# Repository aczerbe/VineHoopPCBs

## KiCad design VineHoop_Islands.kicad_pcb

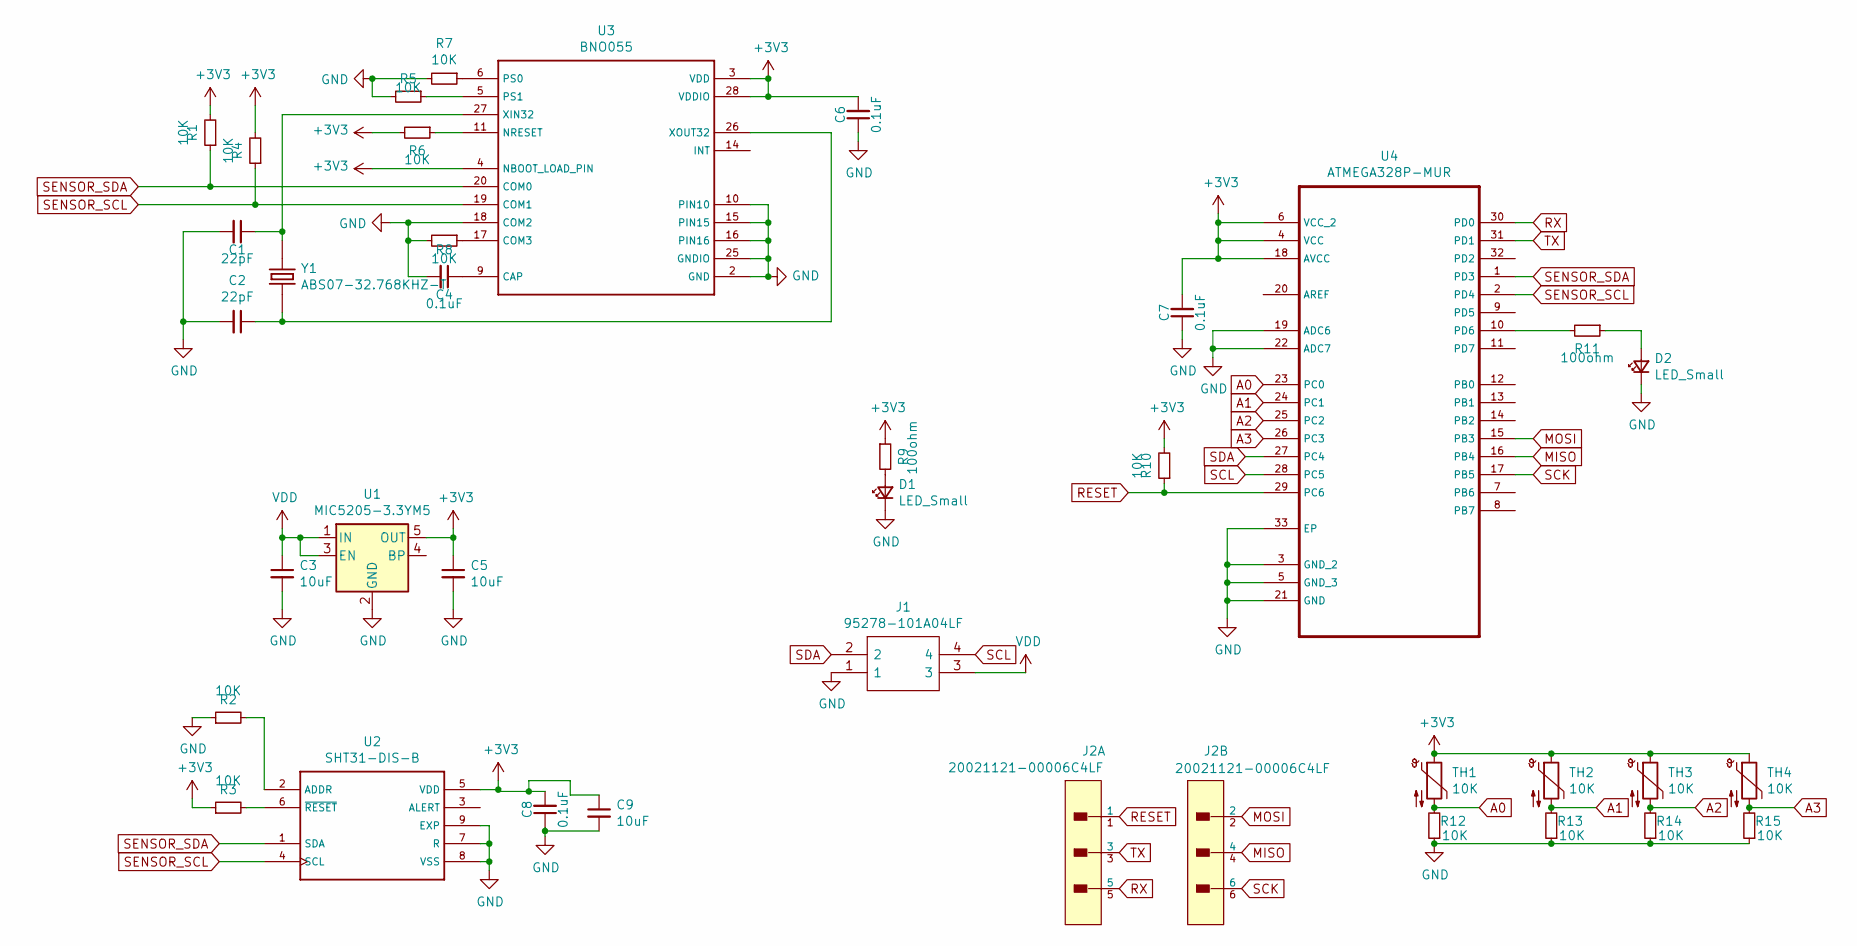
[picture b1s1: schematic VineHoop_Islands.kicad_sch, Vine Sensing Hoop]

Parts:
C1, C2: 22pF; C_0603_1608Metric
C3, C5, C9: 10uF; C_0603_1608Metric
C4, C6, C7, C8: 0.1uF; C_0603_1608Metric
D1, D2: LED_Small; LED_0603_1608Metric
J1: 95278-101A04LF; 95278101A04LF; Manufacturer_Part_Number 95278-101A04LF; Mouser Part Number 649-95278-101A04LF
J2: 20021121-00006C4LF; Amphenol_ICC___FCI-20021121-00006C4LF-MFG; current rating 1A; voltage rating 125V; mouser part number 649-202112100006C4LF; digikey description CONN HEADER SMD 6POS 1.27MM
R1, R2, R3, R4, R5, R6, R7, R8, R10, R12, R13, R14, R15: 10K; R_0603_1608Metric
R9, R11: 100ohm; R_0603_1608Metric
TH1, TH2, TH3, TH4: 10K; R_0603_1608Metric
U1: MIC5205-3.3YM5; SOT-23-5
U2: SHT31-DIS-B; XDCR_SHT31-DIS-F2.5KS
U3: BNO055; LGA28R50P4X10_380X520X100
U4: ATMEGA328P-MUR; QFN50P500X500X100-33N
Y1: ABS07-32.768KHZ-T; XTAL_ABS07-32.768KHZ-T

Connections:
+3V3: C5.1, C6.2, C7.2, C8.2, C9.1, R1.2, R3.1, R4.2, R6.2, R9.1, R10.2, TH1.1, TH2.1, TH3.1, TH4.1, U1.5 (OUT), U2.5 (VDD), U3.3 (VDD), U3.4 (NBOOT_LOAD_PIN), U3.28 (VDDIO), U4.4 (VCC), U4.6 (VCC_2), U4.18 (AVCC)
A0: R12.2, TH1.2, U4.23 (PC0)
A1: R13.2, TH2.2, U4.24 (PC1)
A2: R14.2, TH3.2, U4.25 (PC2)
A3: R15.2, TH4.2, U4.26 (PC3)
GND: C1.2, C2.2, C3.2, C4.2, C5.2, C6.1, C7.1, C8.1, C9.2, D1.1 (K), D2.1 (K), J1.1, R2.1, R5.2, R7.2, R8.2, R12.1, R13.1, R14.1, R15.1, U1.2 (GND), U2.7 (R), U2.8 (VSS), U2.9 (EXP), U3.2 (GND), U3.10 (PIN10), U3.15 (PIN15), U3.16 (PIN16), U3.18 (COM2), U3.25 (GNDIO), U4.3 (GND_2), U4.5 (GND_3), U4.19 (ADC6), U4.21 (GND), U4.22 (ADC7), U4.33 (EP)
MISO: J2.4, U4.16 (PB4)
MOSI: J2.2, U4.15 (PB3)
unnamed: C1.1, U3.27 (XIN32), Y1.1
unnamed: C2.1, U3.26 (XOUT32), Y1.2
unnamed: C4.1, U3.9 (CAP)
unnamed: D1.2 (A), R9.2
unnamed: D2.2 (A), R11.1
unnamed: R2.2, U2.2 (ADDR)
unnamed: R3.2, U2.6 (~RESET~)
unnamed: R5.1, U3.5 (PS1)
unnamed: R6.1, U3.11 (NRESET)
unnamed: R7.1, U3.6 (PS0)
unnamed: R8.1, U3.17 (COM3)
unnamed: R11.2, U4.10 (PD6)
RESET: J2.1, R10.1, U4.29 (PC6)
RX: J2.5, U4.30 (PD0)
SCK: J2.6, U4.17 (PB5)
SCL: J1.4, U4.28 (PC5)
SDA: J1.2, U4.27 (PC4)
SENSOR_SCL: R4.1, U2.4 (SCL), U3.19 (COM1), U4.2 (PD4)
SENSOR_SDA: R1.1, U2.1 (SDA), U3.20 (COM0), U4.1 (PD3)
TX: J2.3, U4.31 (PD1)
VDD: C3.1, J1.3, U1.1 (IN), U1.3 (EN)

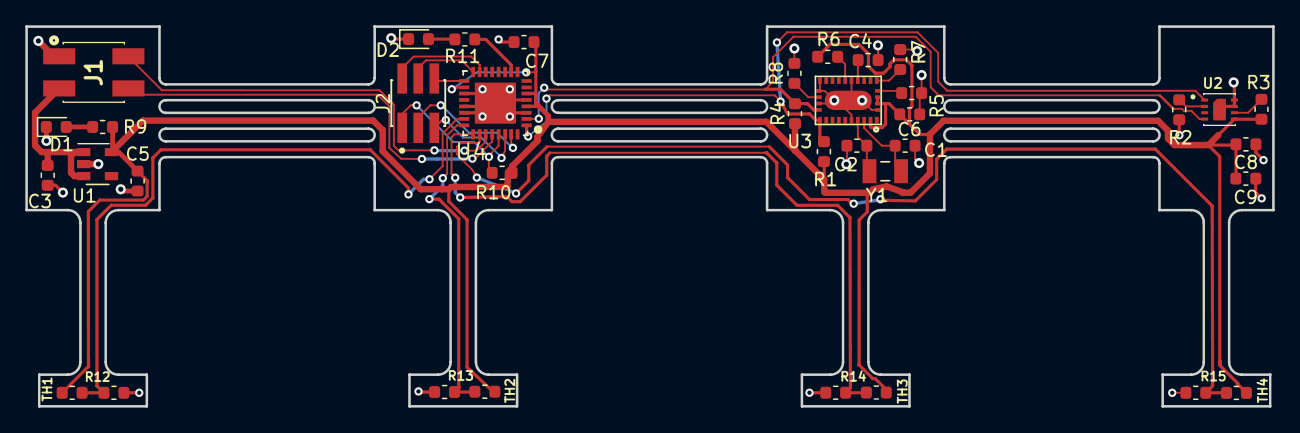
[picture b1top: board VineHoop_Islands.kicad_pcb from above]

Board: 2 copper layers, 98.5 x 30.0 mm, 37 parts (0 on the bottom side), 29 nets.

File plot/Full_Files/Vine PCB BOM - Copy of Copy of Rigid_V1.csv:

Item,Designator,Qty,Manufacturer,Manufacturer P/N,Description
1,"C1, C2, C7, C8",4,Yageo,CC0603JRNPO9BN220,22pF ceramic cap (any is fine)
2,"C3, C5",2,AVX Corporation,F981A106MMA,10uF tantalum cap (any is fine)
3,"C4, C6, C9",3,KEMET,C0603C104Z3VACTU,0.1uF ceramic (any is fine)
4,"D1, D2",2,Broadcom Limited,HSMC-C190,LED indicators
5,"J1, J2",2,Sullins Connector Solutions,NPTC061KFXC-RC,"1x06 0.1"" pitch SMD header"
6,J3,1,Sullins Connector Solutions,NPTC041KFXC-RC,"1x04 0.1"" pitch SMD header"
7,"R1, R2, R3, R4, R5, R6, R7, R8, R9",9,Yageo,RC0603FR-0710KL,10K
8,"R10, R11",2,Yageo,RC0603FR-07100RL,100ohm
9,U1,1,Microchip Technology,MIC5205-3.3YM5-TR,MIC5205-3.3YM5 3.3v regulator
10,U2,1,Sensirion AG,SHT31-DIS-B2.5KS,SHT31-DIS-B Temp/Humidity Sensor
11,U3,1,Bosch Sensortec,BNO055,Bosch BNO055 IMU
12,U4,1,Microchip Technology,ATMEGA328P-MU,ATMEGA328P-MU Microcontroller
13,Y1,1,EPSON,FC-135 32.7680KA-A5,32.768kHz
14,Y2,1,TXC CORPORATION,7A-16.000MAAE-T,16MHz Crystal

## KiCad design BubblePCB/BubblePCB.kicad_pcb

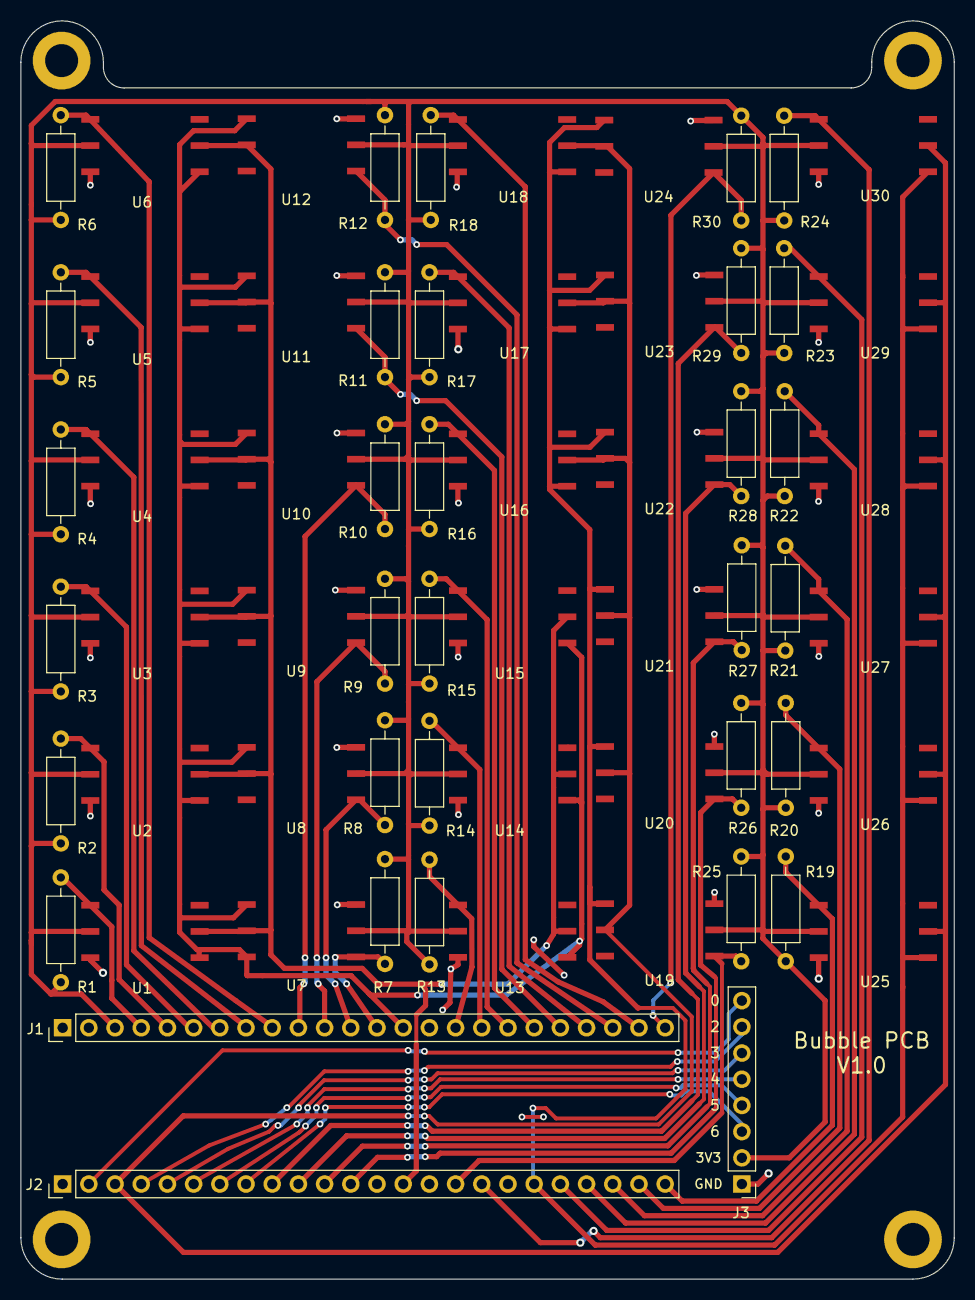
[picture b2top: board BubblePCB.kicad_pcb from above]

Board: 2 copper layers, 90.5 x 122.0 mm, 64 parts (0 on the bottom side), 44 nets.

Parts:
J1, J2: Conn_01x24_Female; PinHeader_1x24_P2.54mm_Vertical
J3: Conn_01x07_Male; PinHeader_1x08_P2.54mm_Vertical
R1, R2, R3, R4, R5, R6, R7, R8, R9, R10, R11, R12, R13, R14, R15, R16, R17, R18, R19, R20, R21, R22, R23, R24, R25, R26, R27, R28, R29, R30: 3.3k; R_Axial_DIN0207_L6.3mm_D2.5mm_P10.16mm_Horizontal
U1, U2, U3, U4, U5, U6, U7, U8, U9, U10, U11, U12, U13, U14, U15, U16, U17, U18, U19, U20, U21, U22, U23, U24, U25, U26, U27, U28, U29, U30: ABPMANN060KGSA3
a: MountingHole_3.2mm_M3_DIN965_Pad

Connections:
+3V3: J1.3, J2.15, J3.2, R1.2, R2.2, R3.2, R4.2, R5.2, R6.2, R7.2, R8.2, R9.2, R10.2, R11.2, R12.2, R13.2, R14.2, R15.2, R16.2, R17.2, R18.2, R19.2, R20.2, R21.2, R22.2, R23.2, R24.2, R25.2, R26.2, R27.2, R28.2, R29.2, R30.2, U1.2 (Vcc), U2.2 (Vcc), U3.2 (Vcc), U4.2 (Vcc), U5.2 (Vcc), U6.2 (Vcc), U7.2 (Vcc), U8.2 (Vcc), U9.2 (Vcc), U10.2 (Vcc), U11.2 (Vcc), U12.2 (Vcc), U13.2 (Vcc), U14.2 (Vcc), U15.2 (Vcc), U16.2 (Vcc), U17.2 (Vcc), U18.2 (Vcc), U19.2 (Vcc), U20.2 (Vcc), U21.2 (Vcc), U22.2 (Vcc), U23.2 (Vcc), U24.2 (Vcc), U25.2 (Vcc), U26.2 (Vcc), U27.2 (Vcc), U28.2 (Vcc), U29.2 (Vcc), U30.2 (Vcc)
GND: J1.2, J1.15, J2.1, J3.1, U1.1 (GND), U2.1 (GND), U3.1 (GND), U4.1 (GND), U5.1 (GND), U6.1 (GND), U7.1 (GND), U8.1 (GND), U9.1 (GND), U10.1 (GND), U11.1 (GND), U12.1 (GND), U13.1 (GND), U14.1 (GND), U15.1 (GND), U16.1 (GND), U17.1 (GND), U18.1 (GND), U19.1 (GND), U20.1 (GND), U21.1 (GND), U22.1 (GND), U23.1 (GND), U24.1 (GND), U25.1 (GND), U26.1 (GND), U27.1 (GND), U28.1 (GND), U29.1 (GND), U30.1 (GND)
MISO: J2.14, U1.5 (MISO), U2.5 (MISO), U3.5 (MISO), U4.5 (MISO), U5.5 (MISO), U6.5 (MISO), U7.5 (MISO), U8.5 (MISO), U9.5 (MISO), U10.5 (MISO), U11.5 (MISO), U12.5 (MISO), U13.5 (MISO), U14.5 (MISO), U15.5 (MISO)
MISO1: J2.3, U16.5 (MISO), U17.5 (MISO), U18.5 (MISO), U19.5 (MISO), U20.5 (MISO), U21.5 (MISO), U22.5 (MISO), U23.5 (MISO), U24.5 (MISO), U25.5 (MISO), U26.5 (MISO), U27.5 (MISO), U28.5 (MISO), U29.5 (MISO), U30.5 (MISO)
unnamed: J1.4, R1.1, U1.3 (SS)
unnamed: J1.5, R2.1, U2.3 (SS)
unnamed: U1.4 (NC), U2.4 (NC), U3.4 (NC), U4.4 (NC), U5.4 (NC), U6.4 (NC), U7.4 (NC), U8.4 (NC), U9.4 (NC), U10.4 (NC), U11.4 (NC), U12.4 (NC), U13.4 (NC), U14.4 (NC), U15.4 (NC)
unnamed: U16.4 (NC), U17.4 (NC), U18.4 (NC), U19.4 (NC), U20.4 (NC), U21.4 (NC), U22.4 (NC), U23.4 (NC), U24.4 (NC), U25.4 (NC), U26.4 (NC), U27.4 (NC), U28.4 (NC), U29.4 (NC), U30.4 (NC)
SCK: J1.14, U1.6 (SCLK), U2.6 (SCLK), U3.6 (SCLK), U4.6 (SCLK), U5.6 (SCLK), U6.6 (SCLK), U7.6 (SCLK), U8.6 (SCLK), U9.6 (SCLK), U10.6 (SCLK), U11.6 (SCLK), U12.6 (SCLK), U13.6 (SCLK), U14.6 (SCLK), U15.6 (SCLK)
SCK1: J2.19, U16.6 (SCLK), U17.6 (SCLK), U18.6 (SCLK), U19.6 (SCLK), U20.6 (SCLK), U21.6 (SCLK), U22.6 (SCLK), U23.6 (SCLK), U24.6 (SCLK), U25.6 (SCLK), U26.6 (SCLK), U27.6 (SCLK), U28.6 (SCLK), U29.6 (SCLK), U30.6 (SCLK)
gp1: J2.8, J3.3
gp2: J2.7, J3.4
gp3: J2.6, J3.5
gp4: J2.5, J3.6
gp5: J2.4, J3.7
gp6: J2.2, J3.8
ss3: J1.6, R3.1, U3.3 (SS)
ss4: J1.7, R4.1, U4.3 (SS)
ss5: J1.8, R5.1, U5.3 (SS)
ss6: J1.9, R6.1, U6.3 (SS)
ss7: J1.10, R10.1, U10.3 (SS)
ss8: J1.11, R9.1, U9.3 (SS)
ss9: J1.12, R8.1, U8.3 (SS)
ss10: J1.13, R7.1, U7.3 (SS)
ss11: J1.16, R13.1, U13.3 (SS)
ss12: J1.17, R14.1, U14.3 (SS)
ss13: J1.18, R15.1, U15.3 (SS)
ss14: J1.19, R16.1, U16.3 (SS)
ss15: J1.20, R11.1, U11.3 (SS)
ss16: J1.21, R17.1, U17.3 (SS)
ss17: J1.22, R12.1, U12.3 (SS)
ss18: J1.23, R18.1, U18.3 (SS)
ss19: J1.24, R24.1, U24.3 (SS)
ss20: J2.9, R23.1, U23.3 (SS)
ss21: J2.10, R22.1, U22.3 (SS)
ss22: J2.11, R21.1, U21.3 (SS)
ss23: J2.12, R20.1, U20.3 (SS)
ss24: J2.16, R19.1, U19.3 (SS)
ss25: J2.24, R25.1, U25.3 (SS)
ss26: J2.23, R26.1, U26.3 (SS)
ss27: J2.22, R27.1, U27.3 (SS)
ss28: J2.21, R28.1, U28.3 (SS)
ss29: J2.20, R29.1, U29.3 (SS)
ss30: J2.17, R30.1, U30.3 (SS)

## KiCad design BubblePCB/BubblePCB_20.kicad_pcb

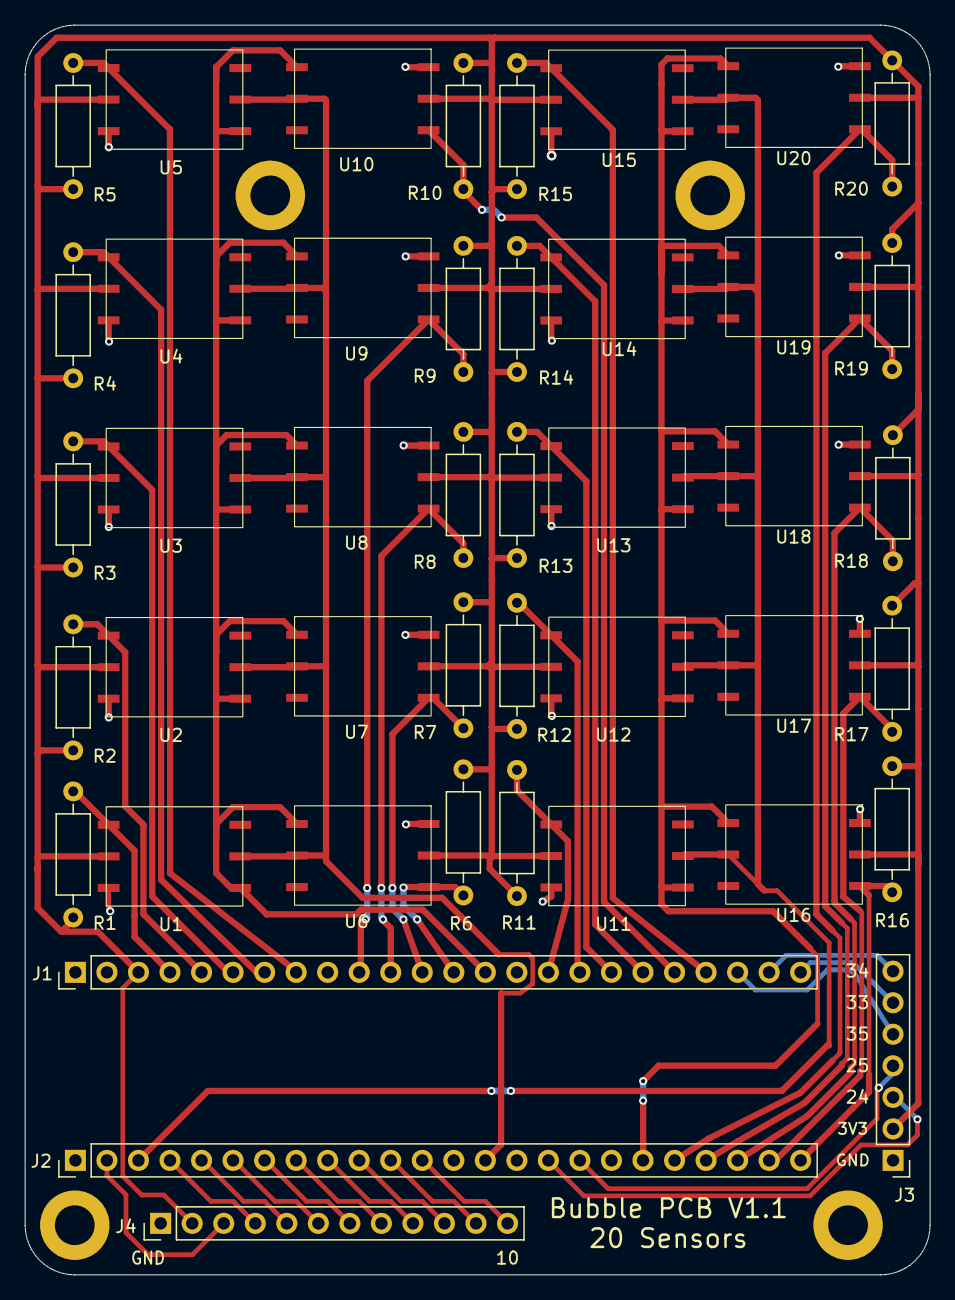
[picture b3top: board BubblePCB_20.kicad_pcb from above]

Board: 2 copper layers, 72.9 x 100.7 mm, 45 parts (0 on the bottom side), 43 nets.

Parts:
J1, J2: Conn_01x24_Female; PinHeader_1x24_P2.54mm_Vertical
J3: Conn_01x07_Male; PinHeader_1x07_P2.54mm_Vertical
J4: PinHeader_1x12_P2.54mm_Vertical
R1, R2, R3, R4, R5, R6, R7, R8, R9, R10, R11, R12, R13, R14, R15, R16, R17, R18, R19, R20: 3.3k; R_Axial_DIN0207_L6.3mm_D2.5mm_P10.16mm_Horizontal
U1, U2, U3, U4, U5, U6, U7, U8, U9, U10, U11, U12, U13, U14, U15, U16, U17, U18, U19, U20: ABPMANN060KGSA3
a: MountingHole_3.2mm_M3_DIN965_Pad

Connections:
+3V3: J1.3, J2.15, J3.2, J4.2, R1.2, R2.2, R3.2, R4.2, R5.2, R6.2, R7.2, R8.2, R9.2, R10.2, R11.2, R12.2, R13.2, R14.2, R15.2, R16.2, R17.2, R18.2, R19.2, R20.2, U1.2 (Vcc), U2.2 (Vcc), U3.2 (Vcc), U4.2 (Vcc), U5.2 (Vcc), U6.2 (Vcc), U7.2 (Vcc), U8.2 (Vcc), U9.2 (Vcc), U10.2 (Vcc), U11.2 (Vcc), U12.2 (Vcc), U13.2 (Vcc), U14.2 (Vcc), U15.2 (Vcc), U16.2 (Vcc), U17.2 (Vcc), U18.2 (Vcc), U19.2 (Vcc), U20.2 (Vcc)
GND: J1.2, J1.15, J2.1, J3.1, J4.1, U1.1 (GND), U2.1 (GND), U3.1 (GND), U4.1 (GND), U5.1 (GND), U6.1 (GND), U7.1 (GND), U8.1 (GND), U9.1 (GND), U10.1 (GND), U11.1 (GND), U12.1 (GND), U13.1 (GND), U14.1 (GND), U15.1 (GND), U16.1 (GND), U17.1 (GND), U18.1 (GND), U19.1 (GND), U20.1 (GND)
MISO: J2.14, U1.5 (MISO), U2.5 (MISO), U3.5 (MISO), U4.5 (MISO), U5.5 (MISO), U6.5 (MISO), U7.5 (MISO), U8.5 (MISO), U9.5 (MISO), U10.5 (MISO)
MISO1: J2.3, U11.5 (MISO), U12.5 (MISO), U13.5 (MISO), U14.5 (MISO), U15.5 (MISO), U16.5 (MISO), U17.5 (MISO), U18.5 (MISO), U19.5 (MISO), U20.5 (MISO)
unnamed: J1.4, R1.1, U1.3 (SS)
unnamed: J1.5, R2.1, U2.3 (SS)
unnamed: U1.4 (NC), U2.4 (NC), U3.4 (NC), U4.4 (NC), U5.4 (NC), U6.4 (NC), U7.4 (NC), U8.4 (NC), U9.4 (NC), U10.4 (NC), U11.4 (NC), U12.4 (NC), U13.4 (NC)
unnamed: U14.4 (NC), U15.4 (NC), U16.4 (NC), U17.4 (NC), U18.4 (NC), U19.4 (NC), U20.4 (NC)
SCK: J1.14, U1.6 (SCLK), U2.6 (SCLK), U3.6 (SCLK), U4.6 (SCLK), U5.6 (SCLK), U6.6 (SCLK), U7.6 (SCLK), U8.6 (SCLK), U9.6 (SCLK), U10.6 (SCLK)
SCK1: J2.19, U11.6 (SCLK), U12.6 (SCLK), U13.6 (SCLK), U14.6 (SCLK), U15.6 (SCLK), U16.6 (SCLK), U17.6 (SCLK), U18.6 (SCLK), U19.6 (SCLK), U20.6 (SCLK)
gp1: J2.16, J3.3
gp2: J2.17, J3.4
gp3: J1.22, J3.5
gp4: J1.24, J3.6
gp5: J1.23, J3.7
gp6: J2.2, J4.3
gp7: J2.4, J4.4
gp8: J2.5, J4.5
gp9: J2.6, J4.6
gp10: J2.7, J4.7
gp11: J2.8, J4.8
gp12: J2.9, J4.9
gp13: J2.10, J4.10
gp14: J2.11, J4.11
gp15: J2.12, J4.12
ss3: J1.6, R3.1, U3.3 (SS)
ss4: J1.7, R4.1, U4.3 (SS)
ss5: J1.8, R5.1, U5.3 (SS)
ss7: J1.10, R9.1, U9.3 (SS)
ss8: J1.11, R8.1, U8.3 (SS)
ss9: J1.12, R7.1, U7.3 (SS)
ss10: J1.13, R6.1, U6.3 (SS)
ss11: J1.16, R11.1, U11.3 (SS)
ss12: J1.17, R12.1, U12.3 (SS)
ss13: J1.18, R13.1, U13.3 (SS)
ss14: J1.19, R14.1, U14.3 (SS)
ss15: J1.20, R10.1, U10.3 (SS)
ss16: J1.21, R15.1, U15.3 (SS)
ss20: J2.20, R20.1, U20.3 (SS)
ss21: J2.21, R19.1, U19.3 (SS)
ss22: J2.22, R18.1, U18.3 (SS)
ss23: J2.23, R17.1, U17.3 (SS)
ss24: J2.24, R16.1, U16.3 (SS)

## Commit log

2020-07-24 First rev spread out flexpcb
2020-07-27 So much stuff
2020-07-29 Lots of changes incl. "final" gerbers for rigid order
2020-08-18 Monday evening commit
    I know this is not how I’m supposed to use Git
2020-08-19 First rough draft of islands
2020-08-20 Minor edits
2020-11-10 Big backup
